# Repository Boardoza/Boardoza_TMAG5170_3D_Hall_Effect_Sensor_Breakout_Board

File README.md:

# Boardoza TMAG5170 3D Hall-Effect Sensor Breakout Board

The **Boardoza TMAG5170** is a high-precision **3D linear hall-effect sensor breakout board** based on the **Texas Instruments TMAG5170**. This device integrates **three independent Hall sensors (X, Y, and Z axes)** along with a precision signal chain and a 12-bit ADC, enabling accurate magnetic field measurement in compact and high-performance systems.

With support for high-speed **SPI communication (up to 10 MHz)** and sampling rates up to **20 ksps**, the TMAG5170 is ideal for real-time direction sensing applications. Integrated diagnostics, angle calculation (CORDIC engine), and an on-chip temperature sensor provide enhanced reliability and system-level drift compensation. This breakout board is perfect for **industrial automation, robotics, motor control, contactless direction sensing, and smart mechatronic systems.**

## [Click here to purchase!](https://www.ozdisan.com/ureticiler/boardoza)

| Front Side | Back Side |
|:---:|:---:|
|  |  |

---

## Key Features

- **High-Precision 3D Magnetic Sensing:** Measures magnetic field on independent X, Y, and Z axes for accurate direction detection.
- **High-Speed SPI Interface:** Supports up to 10 MHz SPI with integrated CRC for secure communication.
- **Integrated Temperature Sensor:** < ±2°C error for system-level thermal compensation.
- **Ultra-Low Power Operation:** 5 nA deep sleep mode and 1.5 µA autonomous wake-up mode.
- **Smart ALERT Pin:** Can trigger conversions or indicate conversion completion.
- **Built-in Diagnostics:** Integrated fault detection and system monitoring features.
- **On-Chip CORDIC Engine:** Provides direct angle calculation with gain and offset correction.

---

## Technical Specifications

**Model:** TMAG5170A1  
**Manufacturer:** Boardoza   
**Manufacturer IC:** Texas Instruments  
**Functions:** 3D Hall-Effect Sensor   
**Input Voltage:** 2.3V – 5.5V DC  
**Interface:** SPI (up to 10 MHz, CRC supported)  
**Magnetic Field Ranges:** ±25 mT / ±50 mT / ±100 mT (selectable)  
**ADC Resolution:** 12-bit  
**Maximum Sampling Rate:** 20 ksps (single axis)  
**Linear Measurement Error:** ±2.6% (max at 25°C)  
**Sensitivity Temperature Drift:** ±2.8% (max)  
**Temperature Sensor Accuracy:** ±2°C (typical)  
**Deep Sleep Current:** 5 nA (typical)  
**Sleep Mode Current:** 1.5 µA (typical)  
**Active Mode Current:** 3.4 mA (typical)  
**Operating Temperature Range:** –40°C to +150°C  
**Board Dimensions:** 20 mm x 20 mm  

---

## Board Pinout

### ( J1 ) SPI Connector

| Pin Number | Pin Name | Description |
|:----------:|:--------:|-------------|
| 1 | nCS | Chip Select (Active Low) |
| 2 | MISO | SPI Data Output |
| 3 | MOSI | SPI Data Input |
| 4 | SCLK | SPI Clock |
| 5 | nALERT | Conversion Status / Trigger Output (Active Low) |

### ( J2 ) Power Connector

| Pin Number | Pin Name | Description |
|:----------:|:--------:|-------------|
| 1 | VCC | 2.3V – 5.5V Power Supply Input |
| 2 | GND | Ground Reference |

---

## Board Dimensions

---

## Step Files

[Boardoza TMAG5170.step](./assets/TMAG5170%20Step.step)

---

## Datasheet

[TMAG5170 Datasheet.pdf](./assets/TMAG5170%20Datasheet.pdf)

---

## Version History

- V1.0.0 - Initial Release

---

## Support

- If you have any questions or need support, please contact **support@boardoza.com**

---

## **License**

This repository contains both hardware and software components:

### **Hardware Design**

[![CC BY-SA 4.0][cc-by-sa-shield]][cc-by-sa]

All hardware design files are licensed under [Creative Commons Attribution-ShareAlike 4.0 International License][cc-by-sa].

[cc-by-sa]: http://creativecommons.org/licenses/by-sa/4.0/
[cc-by-sa-shield]: https://img.shields.io/badge/License-CC%20BY--SA%204.0-lightgrey.svg

### **Software/Firmware**

[![BSD-3-Clause][bsd-shield]][bsd]

All software and firmware are licensed under [BSD 3-Clause License][bsd].

[bsd]: https://opensource.org/licenses/BSD-3-Clause
[bsd-shield]: https://img.shields.io/badge/License-BSD%203--Clause-blue.svg

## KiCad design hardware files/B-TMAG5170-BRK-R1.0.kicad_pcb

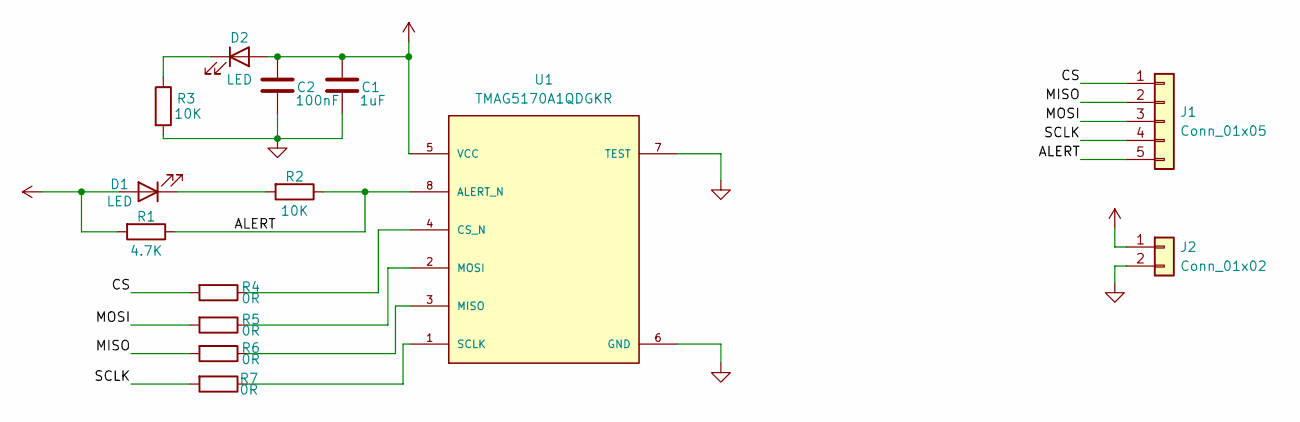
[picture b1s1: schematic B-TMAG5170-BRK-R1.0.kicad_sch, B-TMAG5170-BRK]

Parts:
C1: 1uF; C_0603_1608Metric; MPN CL10A105KO8NNNC
C2: 100nF; C_0603_1608Metric; MPN MCF03KTB500104
D1, D2: LED; LED_0603_1608Metric; MPN LTST-C190KRKT
J1: Conn_01x05; 2317-05S_1x05_P2.50mm_Vertical; MPN 2317-05S
J2: Conn_01x02; 2317-02S_1x02_P2.50mm_Vertical; MPN 2317-02S
R1: 4.7K; R_0603_1608Metric; MPN CRT03F7E4701
R2, R3: 10K; R_0603_1608Metric; MPN CRT03F7E1002
R4, R5, R6, R7: 0R; R_0603_1608Metric; MPN CRT03J7-R0R0
U1: TMAG5170A1QDGKR; DGK0008A-IPC_A; MANUFACTURER_PART_NUMBER TMAG5170A1QDGKR

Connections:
/ALERT: J1.5, R1.1, R2.1, U1.8 (ALERT_N)
/CS: J1.1, R4.2
/MISO: J1.2, R6.2
/MOSI: J1.3, R5.2
/SCLK: J1.4, R7.2
GND: C1.1, C2.1, J2.2, R3.2, U1.6 (GND), U1.7 (TEST)
unnamed: D1.1 (K), R2.2
unnamed: D2.1 (K), R3.1
unnamed: R4.1, U1.4 (CS_N)
unnamed: R6.1, U1.3 (MISO)
unnamed: R5.1, U1.2 (MOSI)
unnamed: R7.1, U1.1 (SCLK)
VCC: C1.2, C2.2, D1.2 (A), D2.2 (A), J2.1, R1.2, U1.5 (VCC)

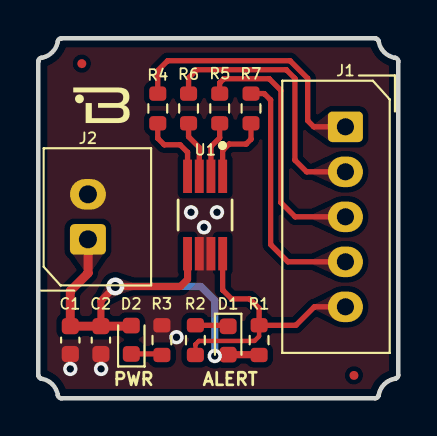
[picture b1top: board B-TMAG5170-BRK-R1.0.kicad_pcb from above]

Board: 2 copper layers, 20.0 x 20.0 mm, 14 parts (0 on the bottom side), 13 nets.

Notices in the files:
parts and their libraries:
COPYRIGHT: Copyright (C) 2022 Ultra Librarian. All rights reserved.
